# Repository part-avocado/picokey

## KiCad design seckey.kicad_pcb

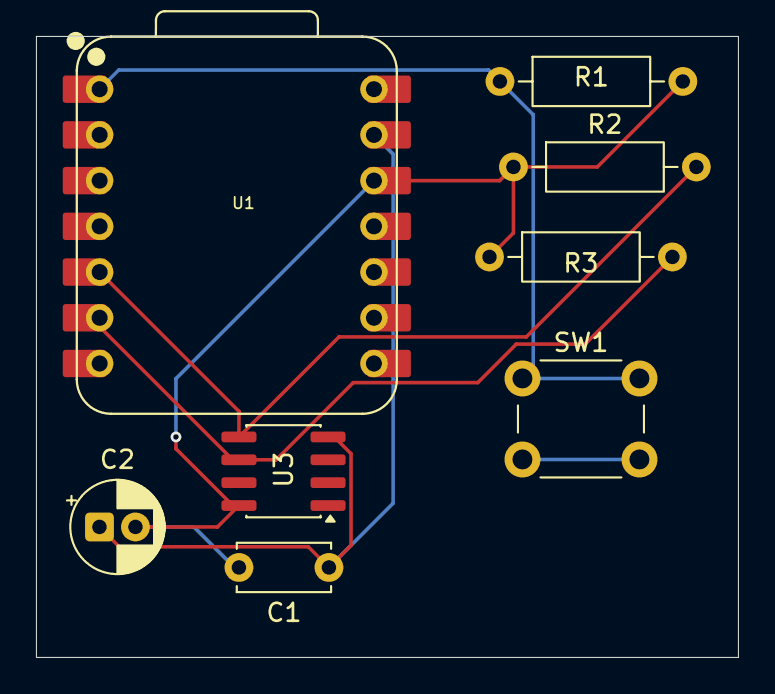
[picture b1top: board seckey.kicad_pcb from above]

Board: 2 copper layers, 39.0 x 34.5 mm, 8 parts (0 on the bottom side), 5 nets.

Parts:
C1: 100nF; C_Disc_D5.0mm_W2.5mm_P5.00mm
C2: 10µF; CP_Radial_D5.0mm_P2.00mm
R1: 10kΩ; R_Axial_DIN0207_L6.3mm_D2.5mm_P10.16mm_Horizontal
R2, R3: 4.7kΩ; R_Axial_DIN0207_L6.3mm_D2.5mm_P10.16mm_Horizontal
SW1: SW_MEC_5E; SW_PUSH_6mm
U1: XIAO-RP2040-DIP
U3: ATECC608A-SSHDA; SOIC-8_3.9x4.9mm_P1.27mm

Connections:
unnamed: C1.1, C2.1, U1.13 (GND), U3.4 (GND)
unnamed: C1.2, C2.2, R1.2, R2.1, R3.1, U1.12 (3V3), U3.8 (VCC)
unnamed: R2.2, U1.5 (GPIO6/SDA), U3.5 (SDA)
unnamed: R3.2, U1.6 (GPIO7/SCL), U3.6 (SCL)
unnamed: R1.1, SW1.1, U1.1 (GPIO26/ADC0/A0)

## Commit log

2025-12-18 x1cc
2025-12-18 things
2025-12-18 items
